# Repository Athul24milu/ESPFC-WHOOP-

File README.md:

# ESPFC WHOOP

ESP FPV / ATHUL - MATRIX40 L4 hardware for a 1S brushed FPV flight-controller project, built around the Seeed XIAO ESP32-S3, MPU-6050 and AT7456E analog OSD.

## Start here

- [User manual](02_Guides/ESP_FPV_ATHUL_Brochure_L4.pdf): connections, configuration, installation and troubleshooting.
- [Assembly and component guide](02_Guides/ESP_FPV_ATHUL_Component_Map_L4.pdf): component values, closeups, pin 1, polarity and hidden XIAO contacts.
- [Purchase BOM](03_BOM_and_Purchase/ESP_FC_L2_Purchase_BOM.xlsx): quantities and Robu, Quartz Components and Evelta links. Search-only links and unconfirmed candidates are marked.
- [All-reference BOM CSV](03_BOM_and_Purchase/ESP_FC_L2_BOM_All_75_References.csv): all 75 board references, including 62 fitted component packages and integral PCB features.
- [Package instructions](START_HERE.txt).

## PCB fabrication

Upload only [the PCB-only Gerber ZIP](01_JLCPCB_UPLOAD/ESP_FC_L4_PCB_ONLY_GERBERS.zip) to JLCPCB for bare-board fabrication. It contains 11 Gerber layers, separate plated/nonplated drill files and PCB order notes. It contains no BOM or component purchasing data. Components are assembled at home.

Order four layers, 40 x 40 mm outline, 1.00 mm FR4, ENIG, white solder mask and black legend. Specify 1 oz / 35 um copper on **all four layers**, including the inner layers. Standard through vias are used; the minimum drill is 0.20 mm. Mounting holes are four 2.10 mm NPTH holes. The measured mounting square is 24.65 mm, rotated 45 degrees in the board view; it is not a 25.5 mm pattern.

L4 restores the original silkscreen exactly: all 1,023 artwork objects match the earlier L2 geometry, text, layers and count. Full CAM, VTX, SA, RX, TX and 1S labels, original polarity symbols, separators and logo are restored. **Every corrected L3 track and via remains unchanged.** All footprints, component values, pad nets and mounting dimensions are unchanged; the L2-named purchase BOM still applies.

Current KiCad checks: **0 electrical DRC errors, 0 unconnected items, 0 schematic parity issues and 0 ERC violations**. The original **46 text warnings** are intentionally visible again (26 text-height and 20 text-thickness). The nine via-centering warnings remain resolved. No PCB DRC checks were disabled or excluded; ERC uses the unchanged project rules. Ask JLCPCB to accept the fine original artwork/proof before ordering; small labels may print poorly. Assembled hardware still requires bench validation.

See [manufacturing notes](02_Guides/MANUFACTURING_README.md) and [verification records](05_Verification/).

## Open the design

Open [ESP_FPV_ATHUL_IOGROUPED.kicad_pro](04_KiCad_Project/ESP_FPV_ATHUL_IOGROUPED.kicad_pro) in KiCad 10. Keep the child schematics, local symbol/footprint libraries and models alongside the project. The project is self-contained apart from KiCad's standard installation libraries.

## Firmware and assembly requirements

No ready-to-fly firmware is included. The L4 pin assignments are **IMU SDA GPIO5, IMU SCL GPIO43 and motor 3 PWM GPIO39**. Default XIAO SCL GPIO6 is PWM4 on this PCB. Configure I2C explicitly, manage UART0 TX output on GPIO43, and initialize motor outputs low before motor power.

Read [the firmware pin map](02_Guides/FIRMWARE_PINMAP.md) and [assembly notes](02_Guides/ASSEMBLY_NOTES.md). C17 is fitted at 220 pF C0G; C20 is 2.2 nF X7R 50 V. The MPU-6050 is a bare QFN-24, not a breakout module. First power should use a current-limited supply with motors disconnected. Remove propellers for output checks.

## Package contents

| Folder | Contents |
| --- | --- |
| `01_JLCPCB_UPLOAD` | PCB-only fabrication ZIP |
| `02_Guides` | User manual, assembly guide, PCB views and engineering notes |
| `03_BOM_and_Purchase` | Purchase workbook and all-reference CSV |
| `04_KiCad_Project` | Current editable PCB, schematic, libraries and models |
| `05_Verification` | KiCad, geometry, mask, via and Gerber checks |

`FILE_MANIFEST_SHA256.json` records checksums for the release package. The PCB images are CAD renders, not photographs. Older layout trials are not included.

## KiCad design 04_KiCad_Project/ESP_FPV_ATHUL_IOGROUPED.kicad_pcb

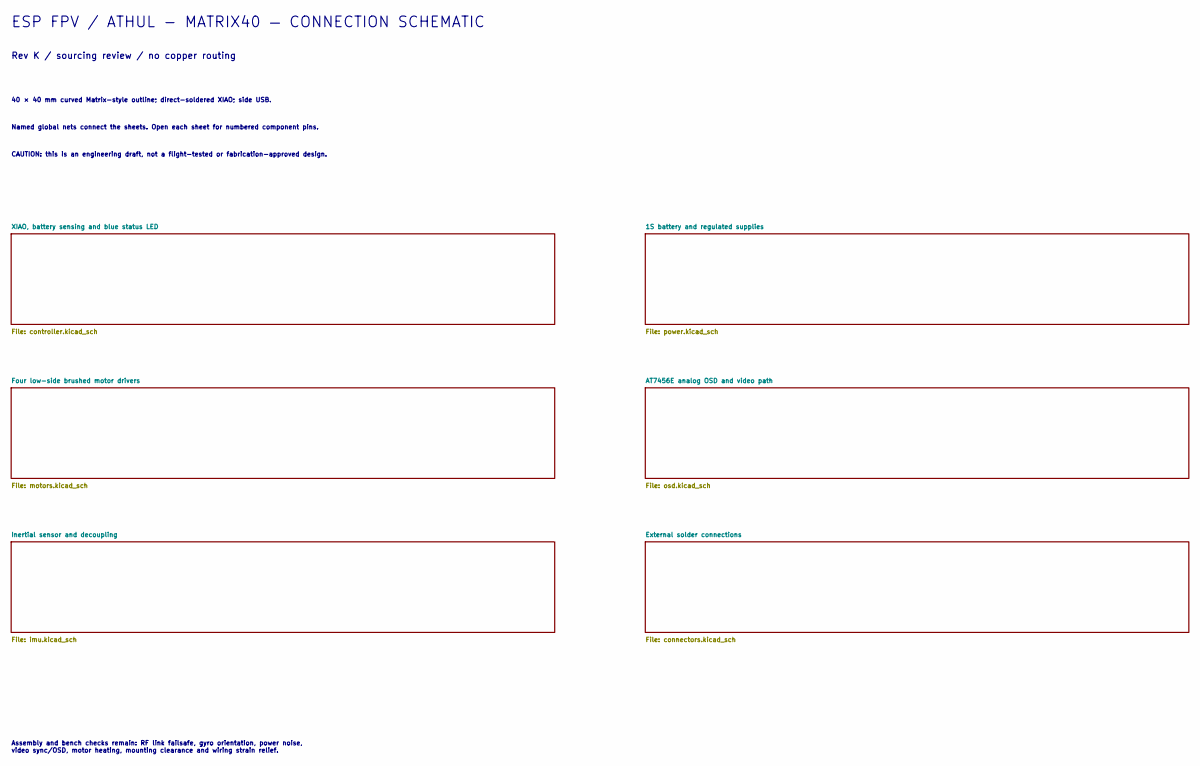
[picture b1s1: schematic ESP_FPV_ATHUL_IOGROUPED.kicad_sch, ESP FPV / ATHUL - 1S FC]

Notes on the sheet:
ESP FPV / ATHUL - MATRIX40 — CONNECTION SCHEMATIC
Rev K / sourcing review / no copper routing
40 × 40 mm curved Matrix-style outline; direct-soldered XIAO; side USB.
Named global nets connect the sheets. Open each sheet for numbered component pins.
CAUTION: this is an engineering draft, not a flight-tested or fabrication-approved design.
Assembly and bench checks remain: RF link failsafe, gyro orientation, power noise, video sync/OSD, motor heating, mounting clearance and wiring strain relief.

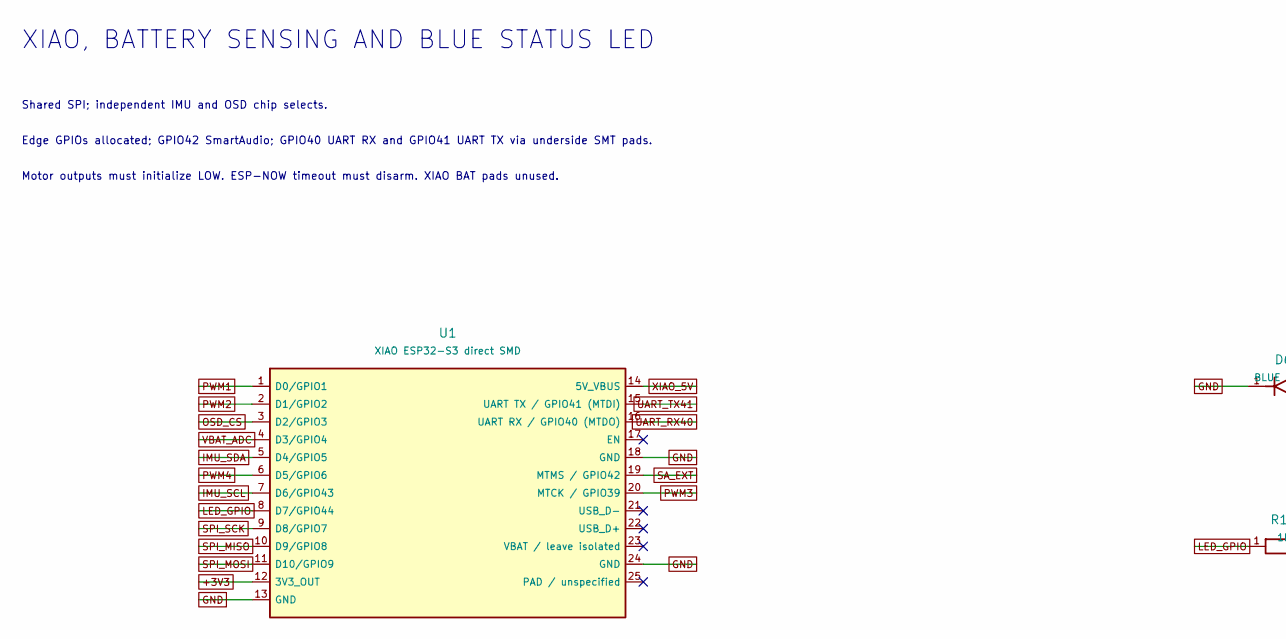
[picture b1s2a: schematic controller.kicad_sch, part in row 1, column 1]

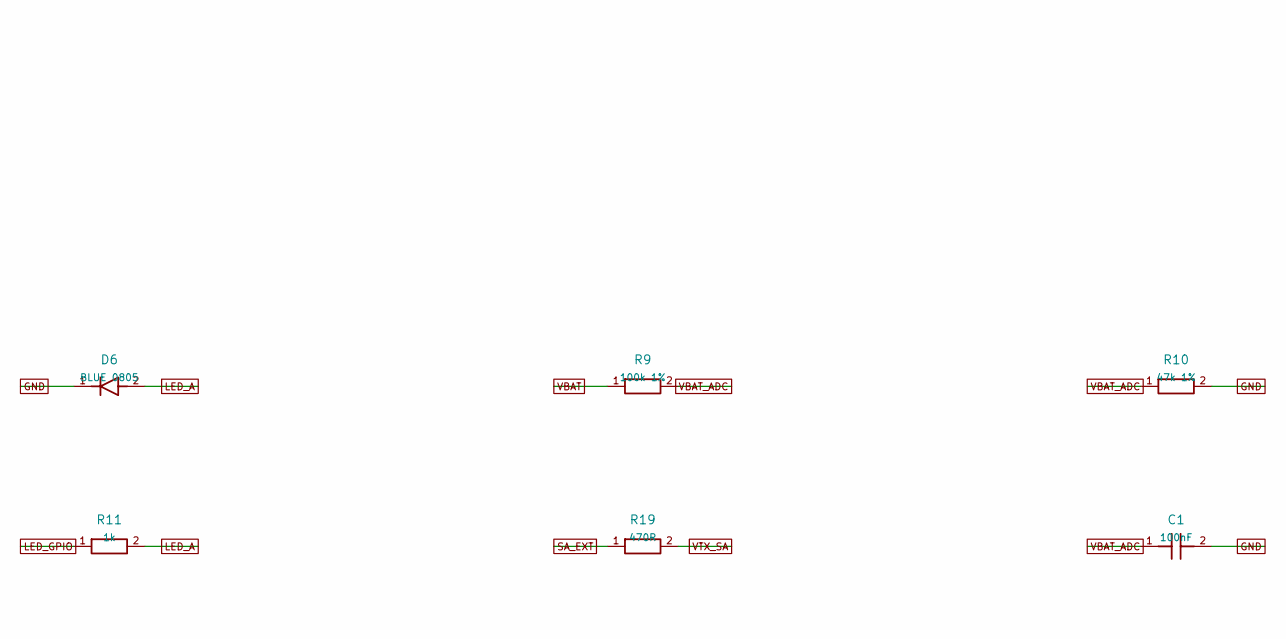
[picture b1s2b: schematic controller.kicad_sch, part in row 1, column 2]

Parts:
C1: 100nF; C_0805_2012Metric_Compact
D6: BLUE 0805; LED_0805_2012Metric_Compact_Assembly
R9: 100k 1%; R_0805_2012Metric_Compact
R10: 47k 1%; R_0805_2012Metric_Compact
R11: 1k; R_0805_2012Metric_Compact
R19: 470R; R_0805_2012Metric_Compact
U1: XIAO ESP32-S3 direct SMD; XIAO_ESP32S3_Direct_SMD_UART

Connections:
+3V3: U1.12 (3V3_OUT); also elsewhere on the board
GND: C1.2, D6.1 (K), R10.2, U1.13 (GND), U1.18 (GND), U1.24 (GND); also elsewhere on the board
IMU_SCL: U1.7 (D6/GPIO43); also elsewhere on the board
IMU_SDA: U1.5 (D4/GPIO5); also elsewhere on the board
LED_A: D6.2 (A), R11.2
LED_GPIO: R11.1, U1.8 (D7/GPIO44)
OSD_CS: U1.3 (D2/GPIO3); also elsewhere on the board
PWM1: U1.1 (D0/GPIO1); also elsewhere on the board
PWM2: U1.2 (D1/GPIO2); also elsewhere on the board
PWM3: U1.20 (MTCK / GPIO39); also elsewhere on the board
PWM4: U1.6 (D5/GPIO6); also elsewhere on the board
SA_EXT: R19.1, U1.19 (MTMS / GPIO42)
SPI_MISO: U1.10 (D9/GPIO8); also elsewhere on the board
SPI_MOSI: U1.11 (D10/GPIO9); also elsewhere on the board
SPI_SCK: U1.9 (D8/GPIO7); also elsewhere on the board
UART_RX40: U1.16 (UART RX / GPIO40 (MTDO)); also elsewhere on the board
UART_TX41: U1.15 (UART TX / GPIO41 (MTDI)); also elsewhere on the board
VBAT: R9.1; also elsewhere on the board
VBAT_ADC: C1.1, R9.2, R10.1, U1.4 (D3/GPIO4)
VTX_SA: R19.2; also elsewhere on the board
XIAO_5V: U1.14 (5V_VBUS); also elsewhere on the board

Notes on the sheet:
XIAO, BATTERY SENSING AND BLUE STATUS LED
Shared SPI; independent IMU and OSD chip selects.
Edge GPIOs allocated; GPIO42 SmartAudio; GPIO40 UART RX and GPIO41 UART TX via underside SMT pads.
Motor outputs must initialize LOW. ESP-NOW timeout must disarm. XIAO BAT pads unused.

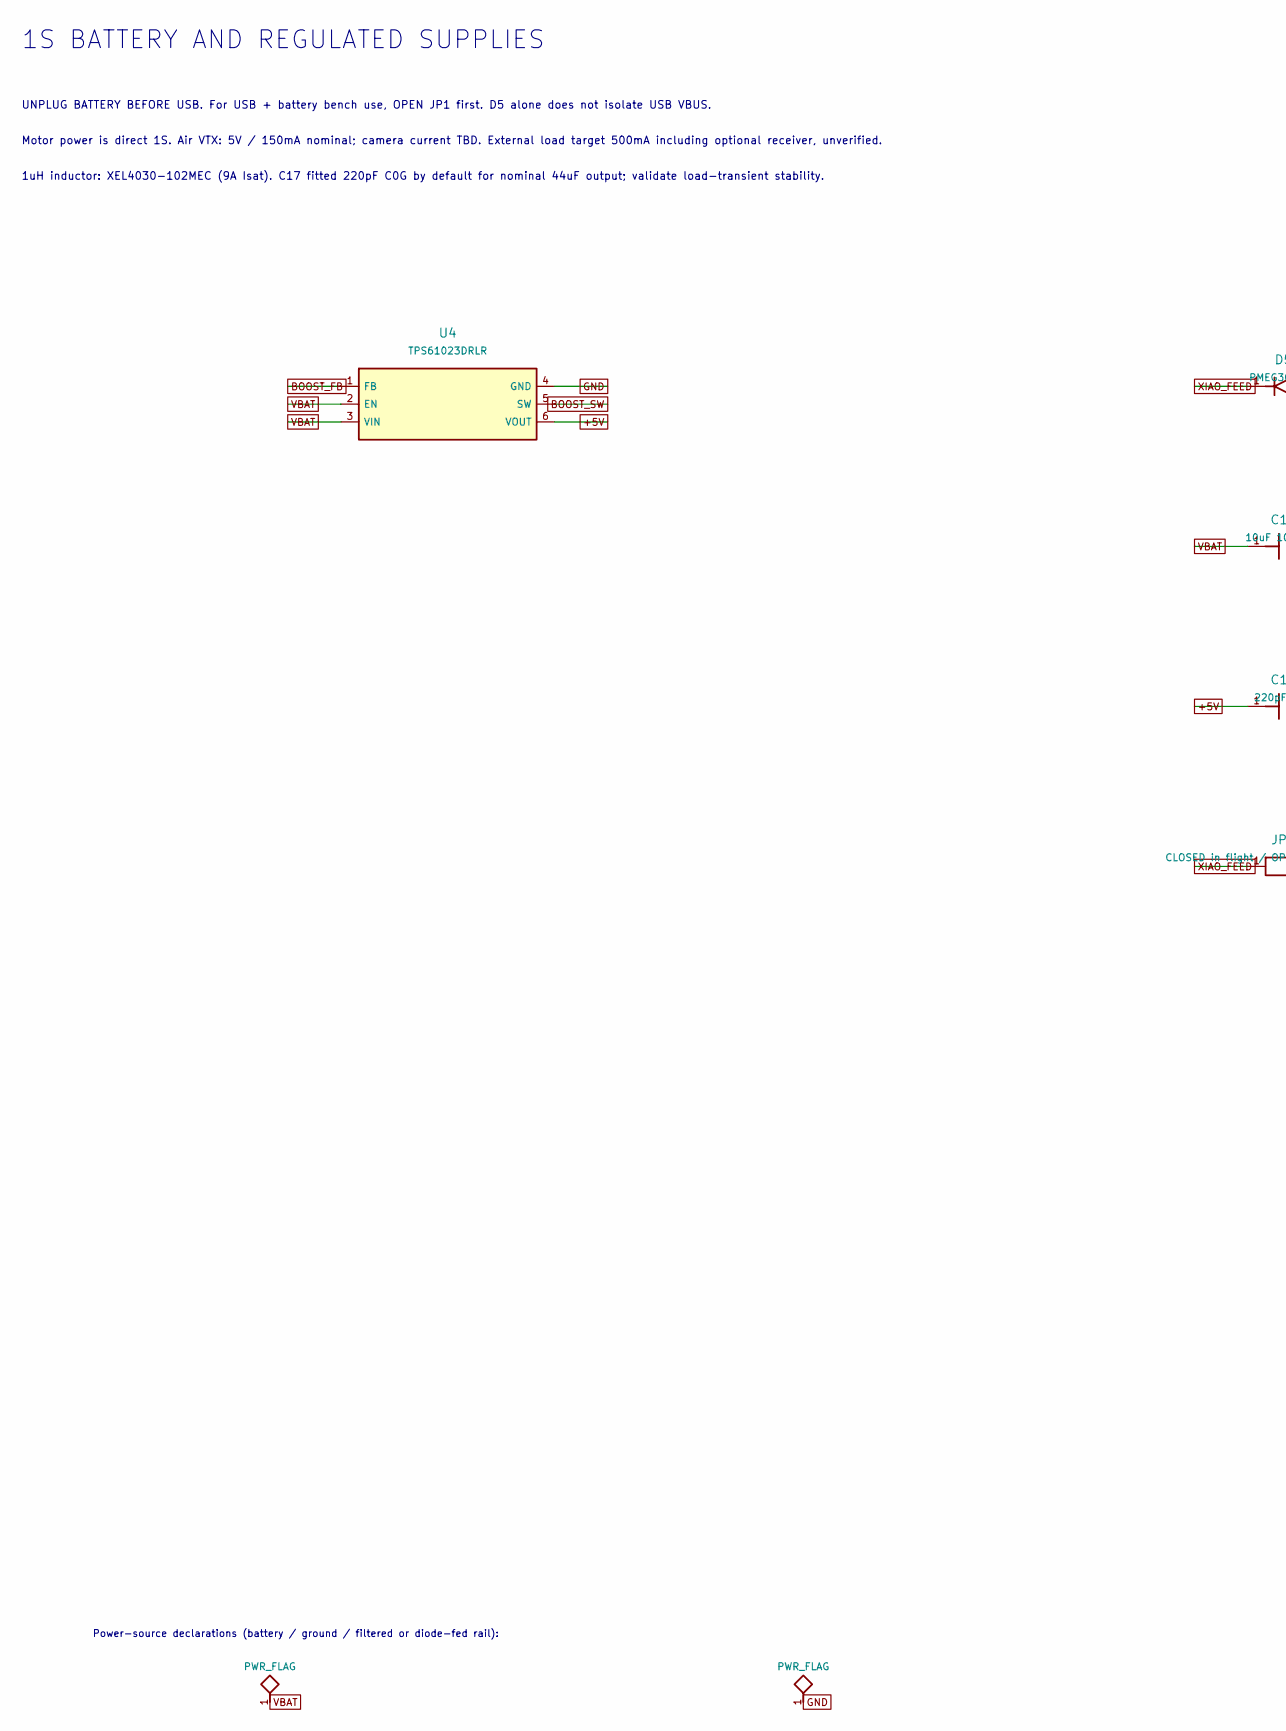
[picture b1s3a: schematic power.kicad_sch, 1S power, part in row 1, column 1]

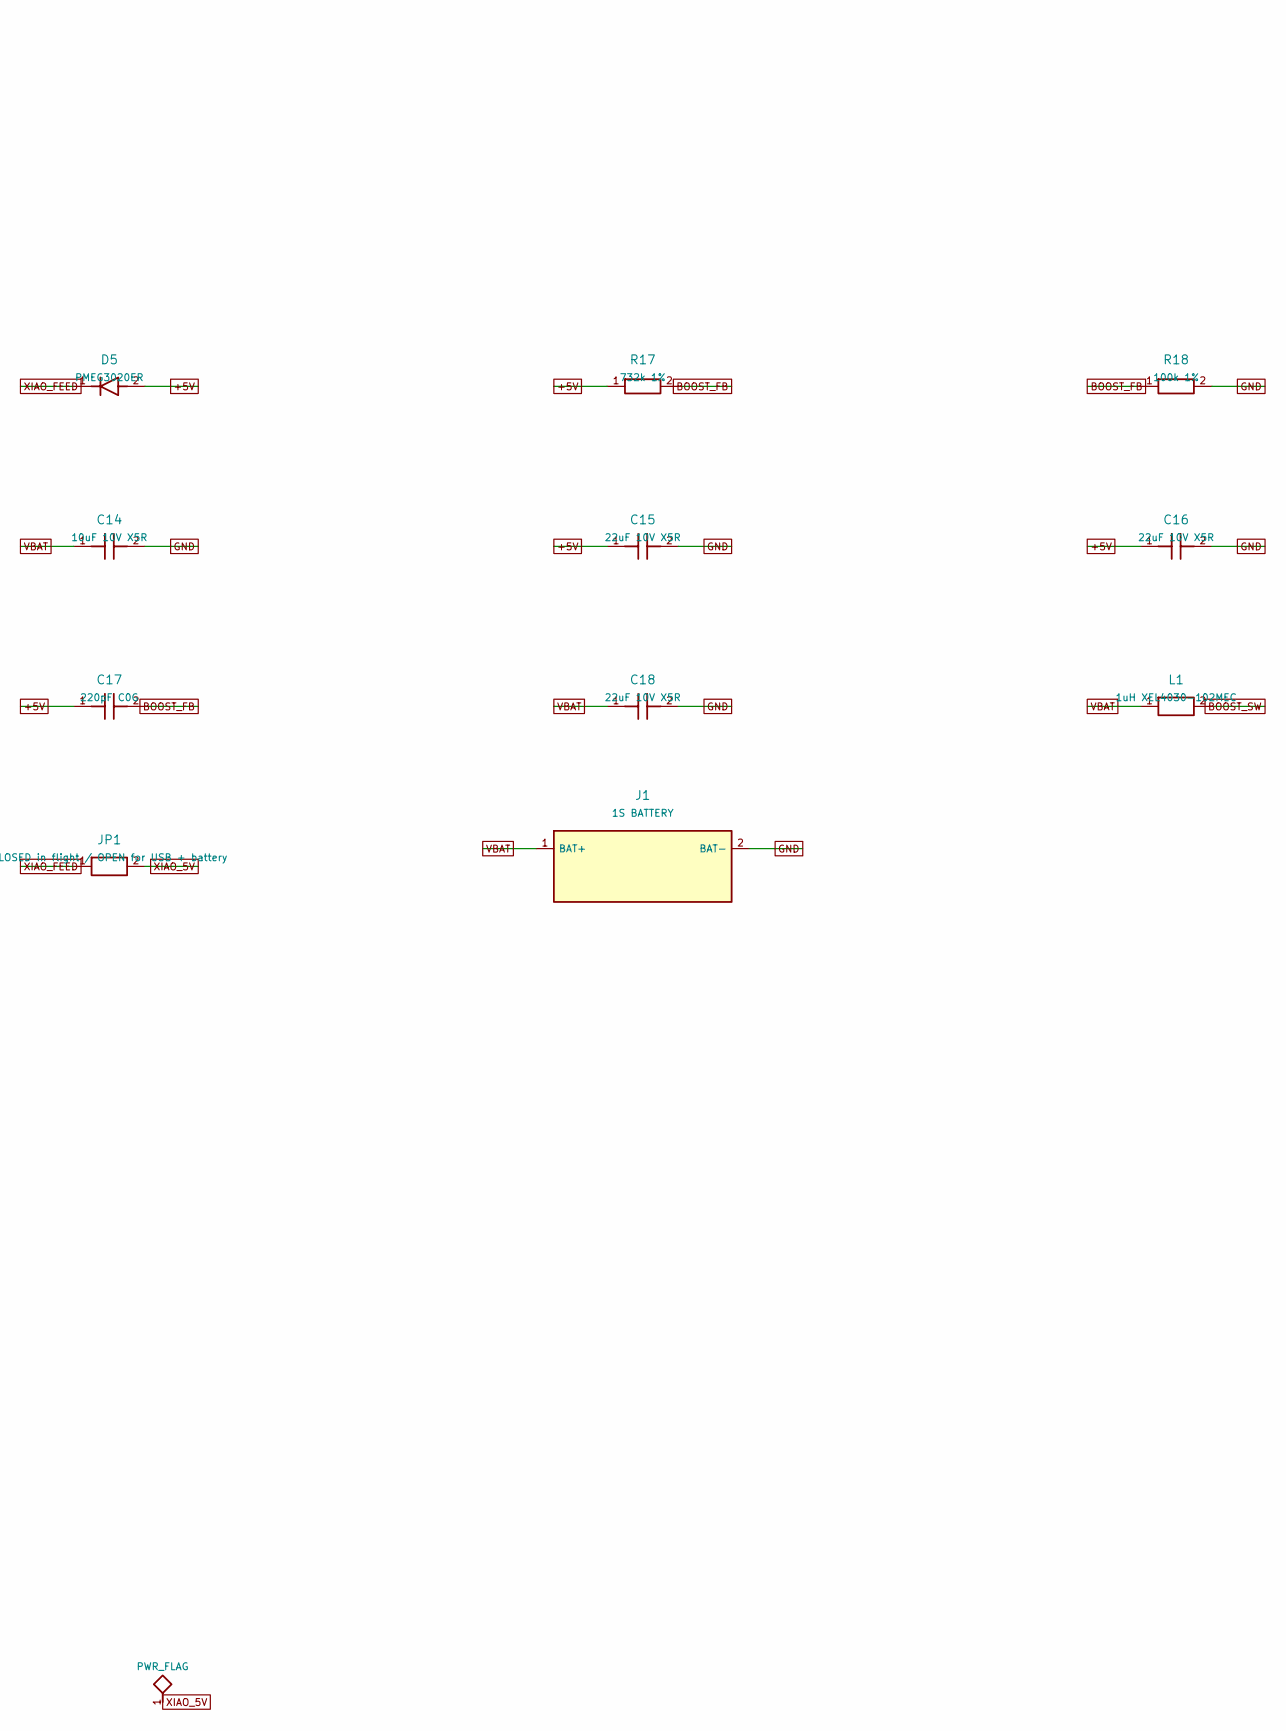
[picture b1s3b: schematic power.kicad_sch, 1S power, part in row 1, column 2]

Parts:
C14: 10uF 10V X5R; C_0805_2012Metric_Compact
C15, C16, C18: 22uF 10V X5R; C_0805_2012Metric_Compact
C17: 220pF C0G; C_0805_2012Metric_Compact
D5: PMEG3020ER; RevK_Assembly_D5
J1: 1S BATTERY; Battery_Pads_2p6
JP1: CLOSED in flight / OPEN for USB + battery; SolderJumper-2_P1.3mm_Bridged_Pad1.0x1.5mm_Compact
L1: 1uH XEL4030-102MEC; L_Coilcraft_XxL4030_Compact
R17: 732k 1%; R_0805_2012Metric_Compact
R18: 100k 1%; R_0805_2012Metric_Compact
U4: TPS61023DRLR; SOT-563_Compact_Assembly

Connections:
+5V: C15.1, C16.1, C17.1, D5.2 (A), R17.1, U4.6 (VOUT); also elsewhere on the board
BOOST_FB: C17.2, R17.2, R18.1, U4.1 (FB)
BOOST_SW: L1.2, U4.5 (SW)
GND: C14.2, C15.2, C16.2, C18.2, J1.2 (BAT-), R18.2, U4.4 (GND); also elsewhere on the board
VBAT: C14.1, C18.1, J1.1 (BAT+), L1.1, U4.2 (EN), U4.3 (VIN); also elsewhere on the board
XIAO_5V: JP1.2; also elsewhere on the board
XIAO_FEED: D5.1 (K), JP1.1

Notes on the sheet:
1S BATTERY AND REGULATED SUPPLIES
UNPLUG BATTERY BEFORE USB. For USB + battery bench use, OPEN JP1 first. D5 alone does not isolate USB VBUS.
Motor power is direct 1S. Air VTX: 5V / 150mA nominal; camera current TBD. External load target 500mA including optional receiver, unverified.
1uH inductor: XEL4030-102MEC (9A Isat). C17 fitted 220pF C0G by default for nominal 44uF output; validate load-transient stability.
Power-source declarations (battery / ground / filtered or diode-fed rail):

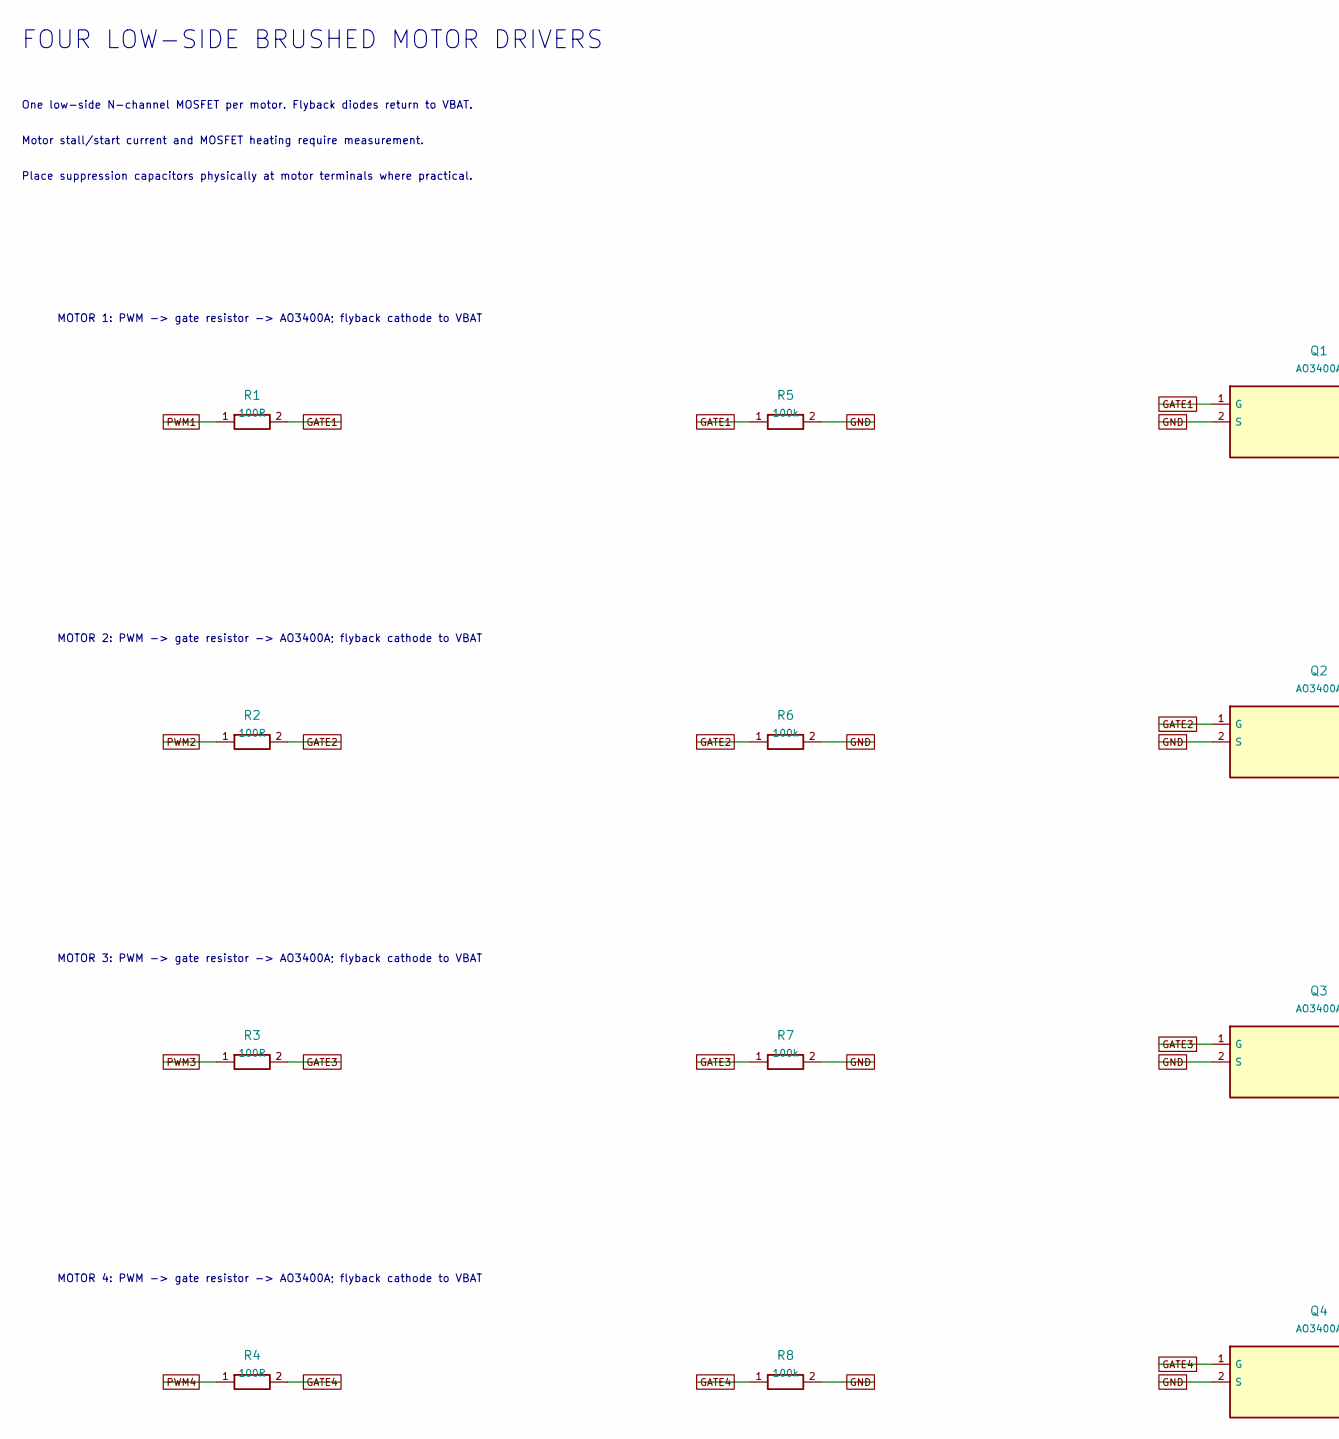
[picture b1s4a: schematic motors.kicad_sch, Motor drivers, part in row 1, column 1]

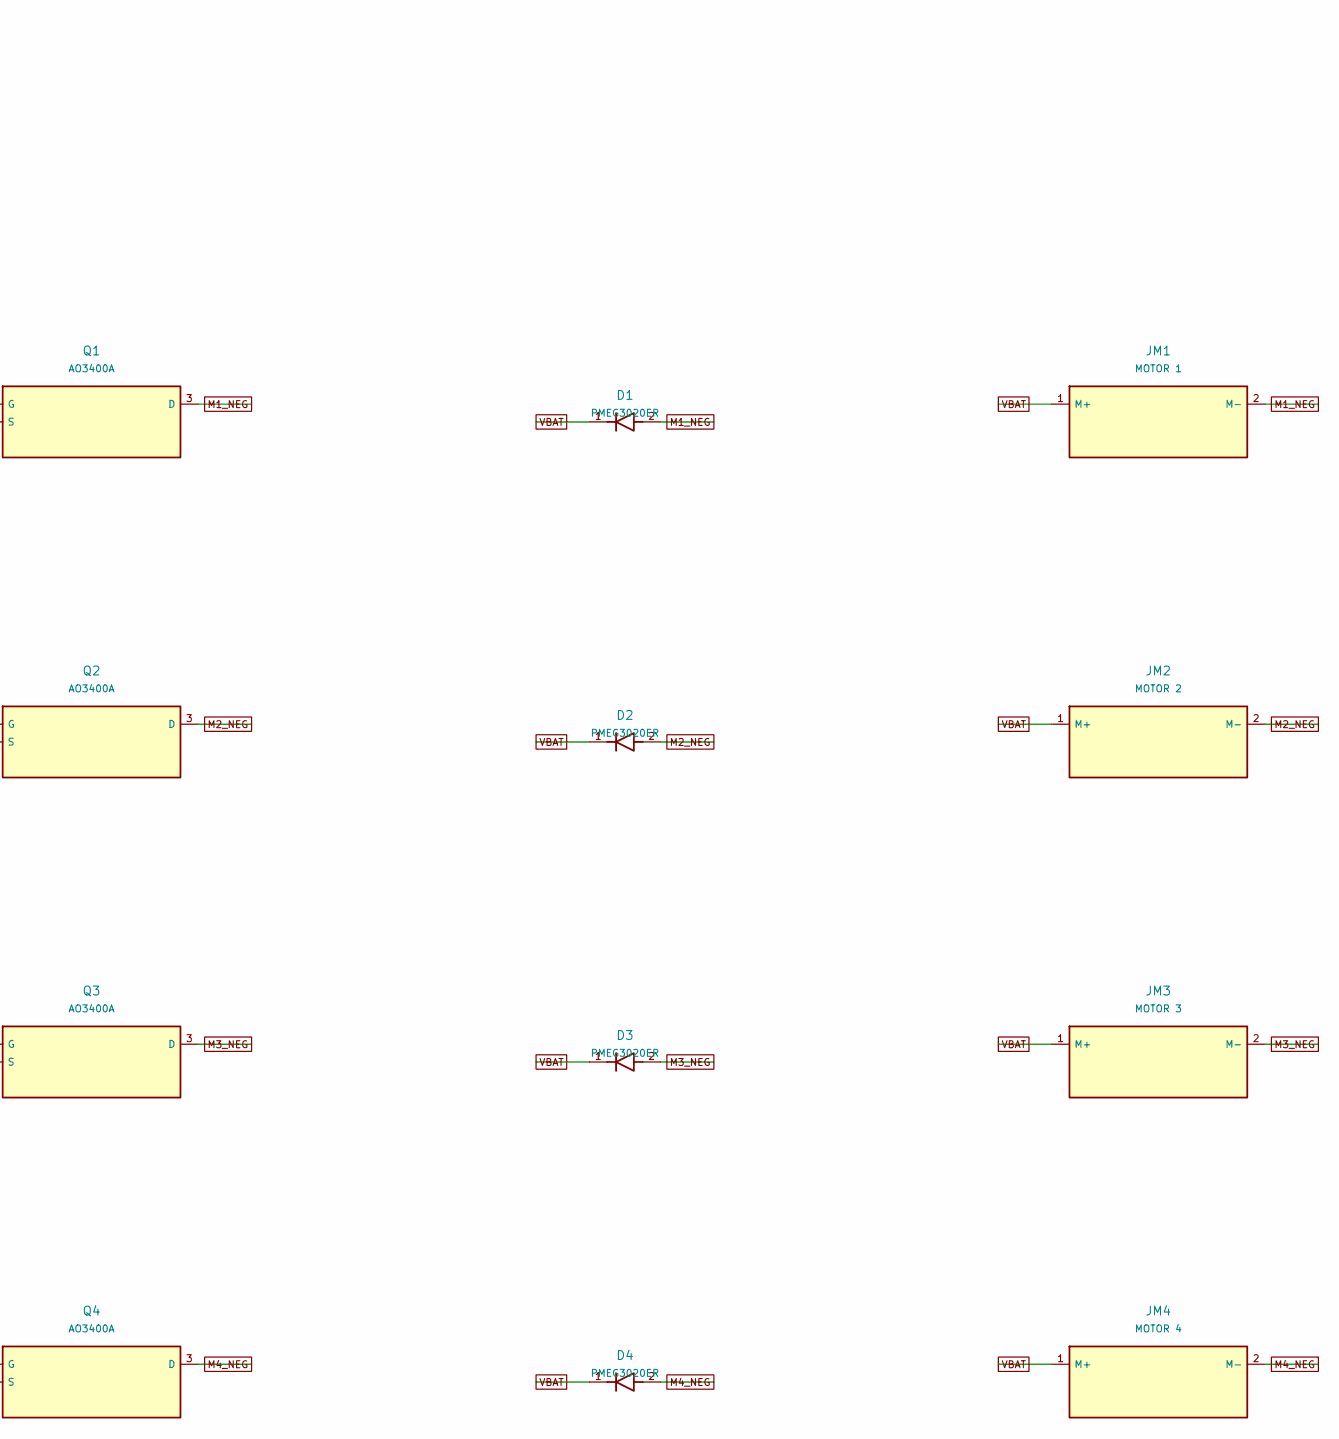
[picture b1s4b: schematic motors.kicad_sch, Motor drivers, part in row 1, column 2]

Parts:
D1: PMEG3020ER; Nexperia_CFP3_SOD-123W_Compact
D2: PMEG3020ER; RevK_Assembly_D2
D3: PMEG3020ER; Nexperia_CFP3_SOD-123W_Compact_Assembly
D4: PMEG3020ER; Nexperia_CFP3_SOD-123W_CurvedEdge
JM1: MOTOR 1; RevK_Assembly_JM1
JM2: MOTOR 2; RevK_Assembly_JM2
JM3: MOTOR 3; RevK_Assembly_JM3
JM4: MOTOR 4; RevK_Assembly_JM4
Q1: AO3400A; RevK_Assembly_Q1
Q2: AO3400A; SOT-23_Compact
Q3: AO3400A; SOT-23_Compact_Assembly
Q4: AO3400A; RevK_Assembly_Q4
R1, R2, R3, R4: 100R; R_0805_2012Metric_Compact
R5, R7: 100k; R_0805_2012Metric_Compact
R6, R8: 100k; R_0805_2012Metric_Compact_Assembly

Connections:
GATE1: Q1.1 (G), R1.2, R5.1
GATE2: Q2.1 (G), R2.2, R6.1
GATE3: Q3.1 (G), R3.2, R7.1
GATE4: Q4.1 (G), R4.2, R8.1
GND: Q1.2 (S), Q2.2 (S), Q3.2 (S), Q4.2 (S), R5.2, R6.2, R7.2, R8.2; also elsewhere on the board
M1_NEG: D1.2 (A), JM1.2 (M-), Q1.3 (D)
M2_NEG: D2.2 (A), JM2.2 (M-), Q2.3 (D)
M3_NEG: D3.2 (A), JM3.2 (M-), Q3.3 (D)
M4_NEG: D4.2 (A), JM4.2 (M-), Q4.3 (D)
PWM1: R1.1; also elsewhere on the board
PWM2: R2.1; also elsewhere on the board
PWM3: R3.1; also elsewhere on the board
PWM4: R4.1; also elsewhere on the board
VBAT: D1.1 (K), D2.1 (K), D3.1 (K), D4.1 (K), JM1.1 (M+), JM2.1 (M+), JM3.1 (M+), JM4.1 (M+); also elsewhere on the board

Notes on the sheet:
FOUR LOW-SIDE BRUSHED MOTOR DRIVERS
One low-side N-channel MOSFET per motor. Flyback diodes return to VBAT.
Motor stall/start current and MOSFET heating require measurement.
Place suppression capacitors physically at motor terminals where practical.
MOTOR 1: PWM -> gate resistor -> AO3400A; flyback cathode to VBAT
MOTOR 2: PWM -> gate resistor -> AO3400A; flyback cathode to VBAT
MOTOR 3: PWM -> gate resistor -> AO3400A; flyback cathode to VBAT
MOTOR 4: PWM -> gate resistor -> AO3400A; flyback cathode to VBAT

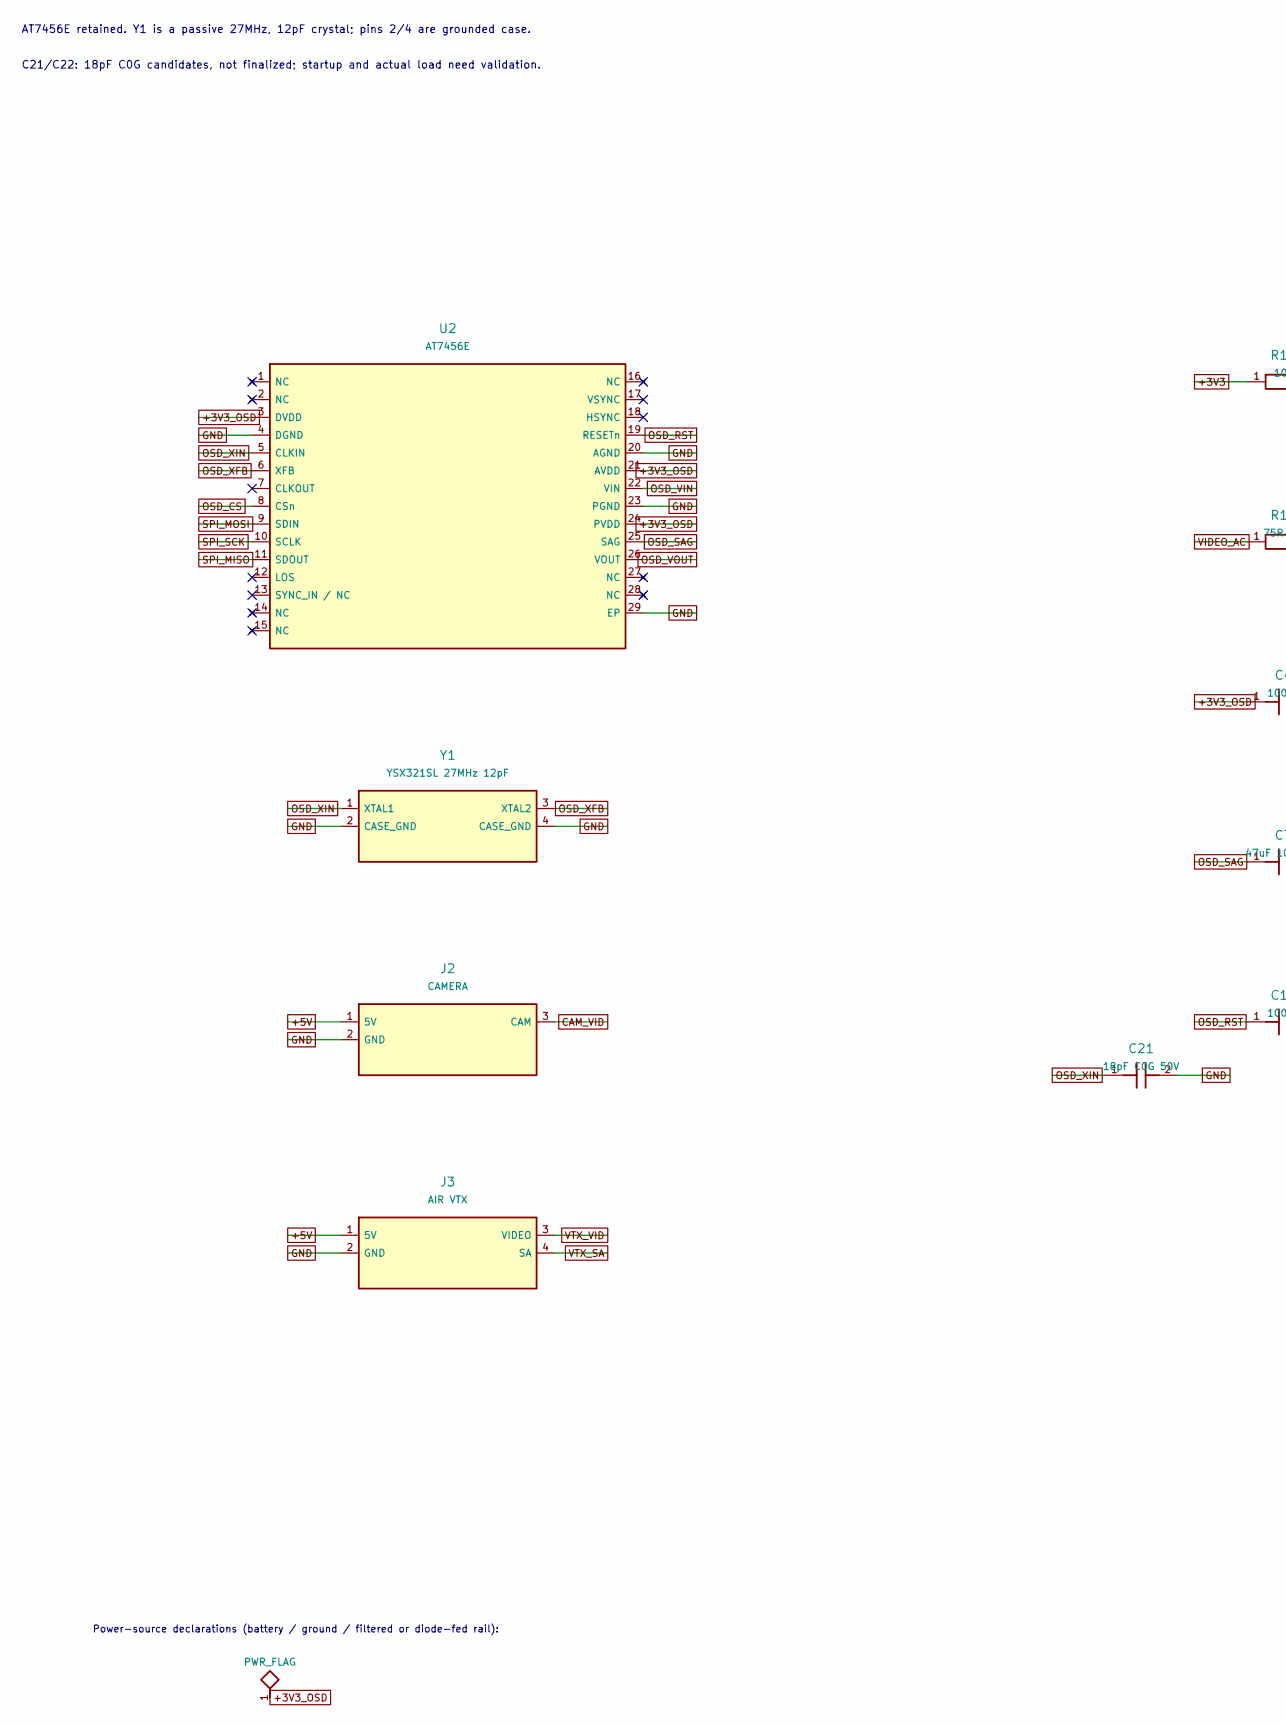
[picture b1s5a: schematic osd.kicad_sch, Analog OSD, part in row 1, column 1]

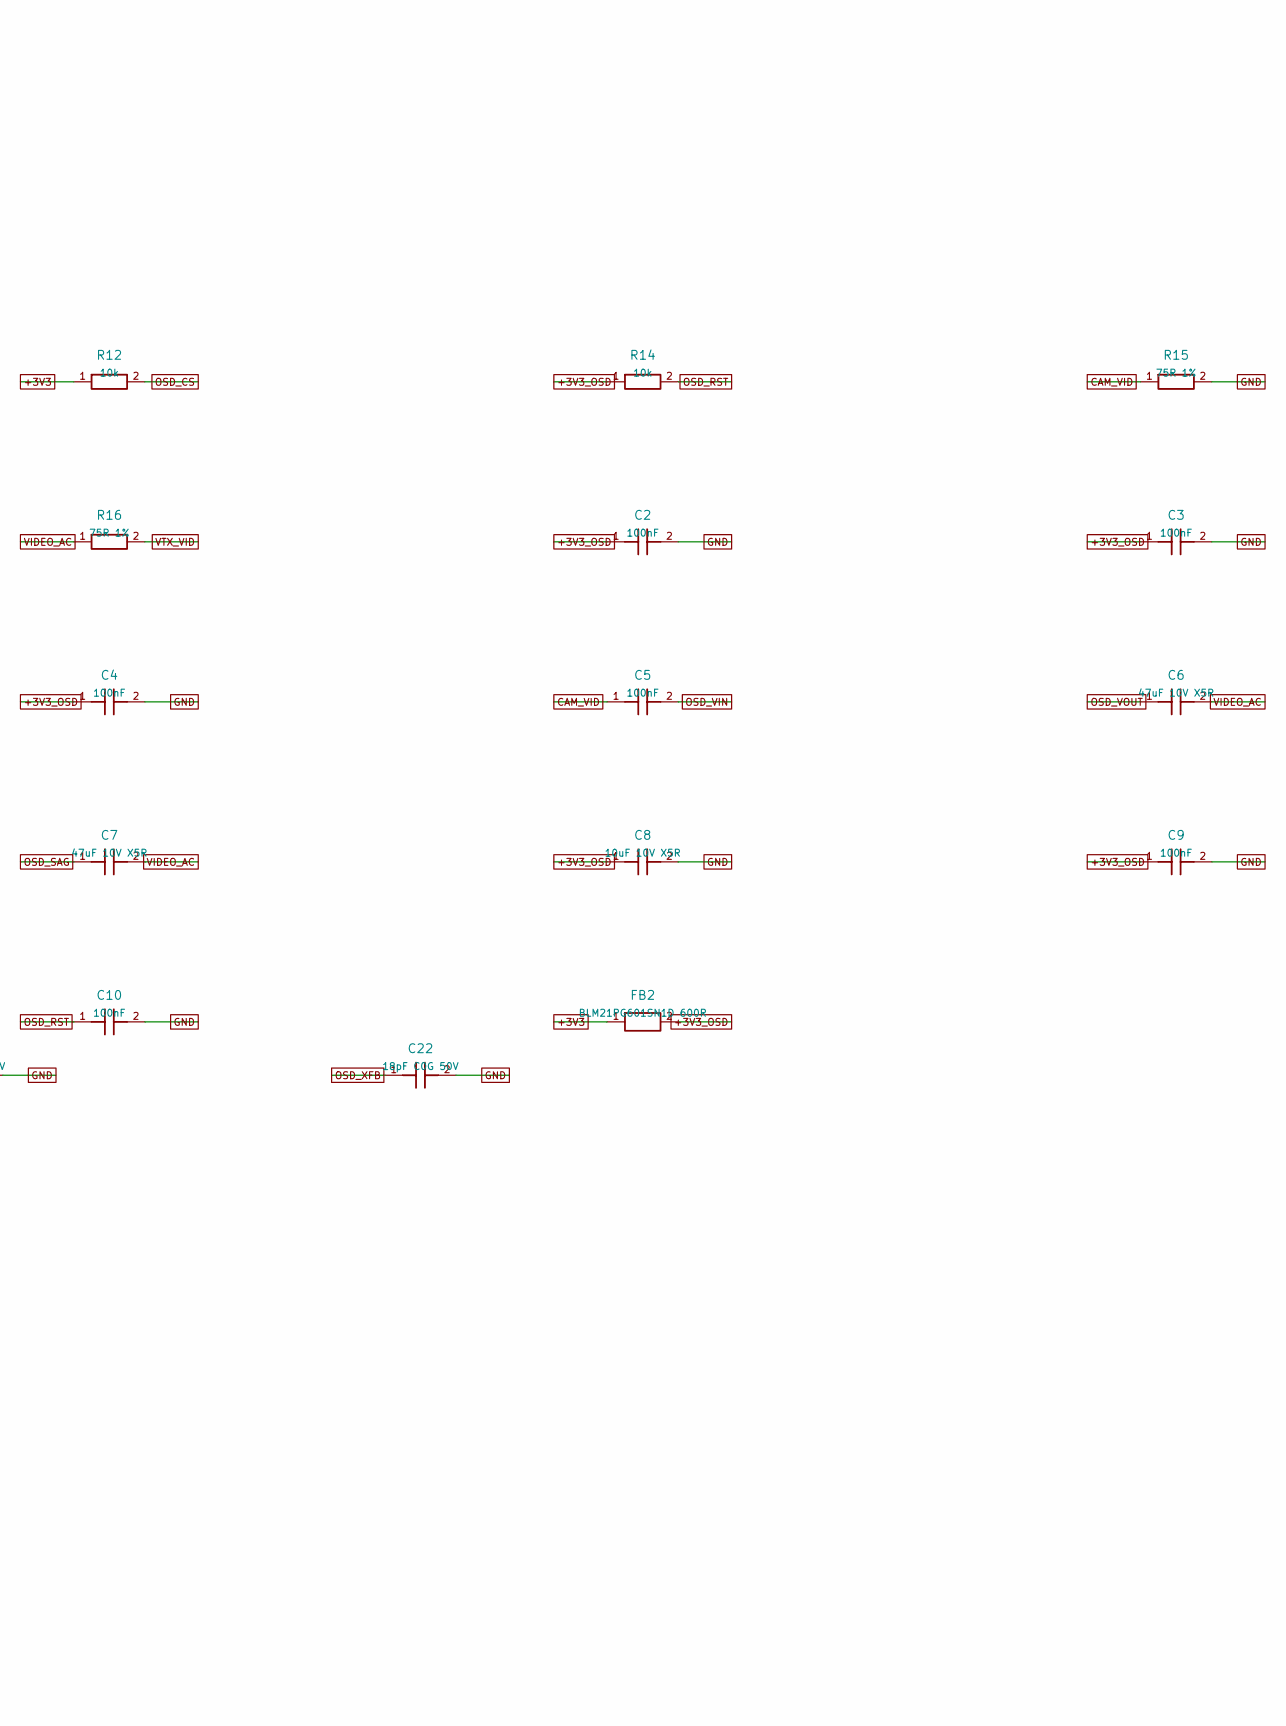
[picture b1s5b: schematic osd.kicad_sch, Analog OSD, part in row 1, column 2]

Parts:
C2, C3, C4, C5, C9, C10: 100nF; C_0805_2012Metric_Compact
C6, C7: 47uF 10V X5R; C_1206_3216Metric_Compact
C8: 10uF 10V X5R; C_0805_2012Metric_Compact
C21, C22: 18pF C0G 50V; C_0805_2012Metric_Compact
FB2: BLM21PG601SN1D 600R; L_0805_2012Metric_Compact
J2: CAMERA; Camera_Pads_1p65
J3: AIR VTX; VTX_Pads_1p65
R12, R14: 10k; R_0805_2012Metric_Compact
R15, R16: 75R 1%; R_0805_2012Metric_Compact
U2: AT7456E; HTSSOP-28-1EP_4.4x9.7mm_P0.65mm_EP2.75x6.2mm_Compact
Y1: YSX321SL 27MHz 12pF; RevK_Assembly_Y1

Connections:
+3V3: FB2.1, R12.1; also elsewhere on the board
+3V3_OSD: C2.1, C3.1, C4.1, C8.1, C9.1, FB2.2, R14.1, U2.3 (DVDD), U2.21 (AVDD), U2.24 (PVDD)
+5V: J2.1 (5V), J3.1 (5V); also elsewhere on the board
CAM_VID: C5.1, J2.3 (CAM), R15.1
GND: C2.2, C3.2, C4.2, C8.2, C9.2, C10.2, C21.2, C22.2, J2.2 (GND), J3.2 (GND), R15.2, U2.4 (DGND), U2.20 (AGND), U2.23 (PGND), U2.29 (EP), Y1.2 (CASE_GND), Y1.4 (CASE_GND); also elsewhere on the board
OSD_CS: R12.2, U2.8 (CSn); also elsewhere on the board
OSD_RST: C10.1, R14.2, U2.19 (RESETn)
OSD_SAG: C7.1, U2.25 (SAG)
OSD_VIN: C5.2, U2.22 (VIN)
OSD_VOUT: C6.1, U2.26 (VOUT)
OSD_XFB: C22.1, U2.6 (XFB), Y1.3 (XTAL2)
OSD_XIN: C21.1, U2.5 (CLKIN), Y1.1 (XTAL1)
SPI_MISO: U2.11 (SDOUT); also elsewhere on the board
SPI_MOSI: U2.9 (SDIN); also elsewhere on the board
SPI_SCK: U2.10 (SCLK); also elsewhere on the board
VIDEO_AC: C6.2, C7.2, R16.1
VTX_SA: J3.4 (SA); also elsewhere on the board
VTX_VID: J3.3 (VIDEO), R16.2

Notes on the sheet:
Power-source declarations (battery / ground / filtered or diode-fed rail):
AT7456E retained. Y1 is a passive 27MHz, 12pF crystal; pins 2/4 are grounded case.
C21/C22: 18pF C0G candidates, not finalized; startup and actual load need validation.
